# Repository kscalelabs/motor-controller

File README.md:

# K-Scale Motor Controller

## `archive/`
Old motor driver designs

## `pcb/`
New designs, focused on EtherCAT compatibility

No documentation yet (oops) but will show up soon<sup>TM</sup> once I can get some of the motor functions validated

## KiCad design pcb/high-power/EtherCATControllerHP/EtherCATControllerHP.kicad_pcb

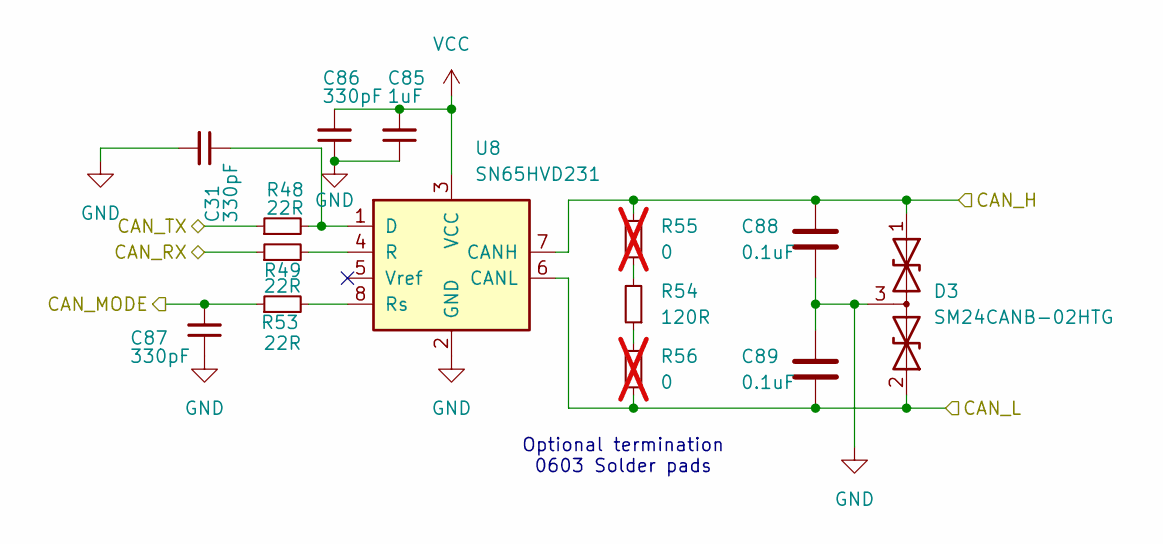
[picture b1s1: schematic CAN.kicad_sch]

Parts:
C31, C86, C87: 330pF; C_0402_1005Metric; LCSC Part # C526998
C85: 1uF; C_0603_1608Metric; LCSC Part # C106858
C88, C89: 0.1uF; C_0603_1608Metric; TOLERANCE ±10%; VOLTAGE - RATED 50V; MANUFACTURER PART NUMBER GRM188R71H104KA93D; LCSC Part # C77055
D3: SM24CANB-02HTG; SOT-23; LCSC Part # C2937019
R48, R49, R53: 22R; R_0603_1608Metric; LCSC Part # C107701
R54: 120R; R_0402_1005Metric; LCSC Part # C114640
R55, R56: 0; R_0603_1608Metric_Pad0.98x0.95mm_HandSolder; not fitted
U8: SN65HVD231; SOIC-8_3.9x4.9mm_P1.27mm; LCSC Part # C129257

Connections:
/CAN_H: C88.1, D3.1 (A1), R55.1, U8.7 (CANH); also elsewhere on the board
/CAN_L: C89.2, D3.2 (A2), R56.2, U8.6 (CANL); also elsewhere on the board
/CAN_MODE: C87.2, R53.1; also elsewhere on the board
/CAN_RX: R49.1; also elsewhere on the board
/CAN_TX: R48.1; also elsewhere on the board
GND: C31.2, C85.1, C86.1, C87.1, C88.2, C89.1, D3.3 (common), U8.2 (GND); also elsewhere on the board
unnamed: R54.1, R56.1
unnamed: R54.2, R55.2
unnamed: C31.1, R48.2, U8.1 (D)
unnamed: R49.2, U8.4 (R)
unnamed: R53.2, U8.8 (Rs)
VCC: C85.2, C86.2, U8.3 (VCC); also elsewhere on the board

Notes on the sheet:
Optional termination 0603 Solder pads

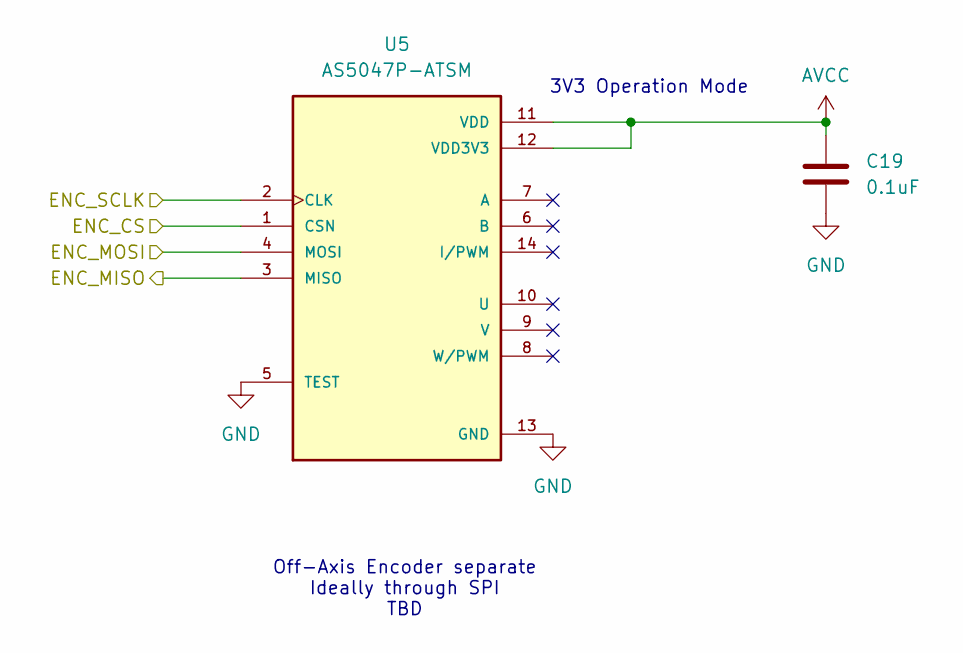
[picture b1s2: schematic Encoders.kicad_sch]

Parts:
C19: 0.1uF; C_0402_1005Metric; LCSC Part # C513772
U5: AS5047P-ATSM; SOP65P640X120-14N; PARTREV 1-01; LCSC Part # C962063

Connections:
/SPI1_CS: U5.1 (CSN); also elsewhere on the board
/SPI1_MISO: U5.3 (MISO); also elsewhere on the board
/SPI1_MOSI: U5.4 (MOSI); also elsewhere on the board
/SPI1_SCK: U5.2 (CLK); also elsewhere on the board
AVCC: C19.1, U5.11 (VDD), U5.12 (VDD3V3); also elsewhere on the board
GND: C19.2, U5.5 (TEST), U5.13 (GND); also elsewhere on the board

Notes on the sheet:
Off-Axis Encoder separate Ideally through SPI TBD
3V3 Operation Mode

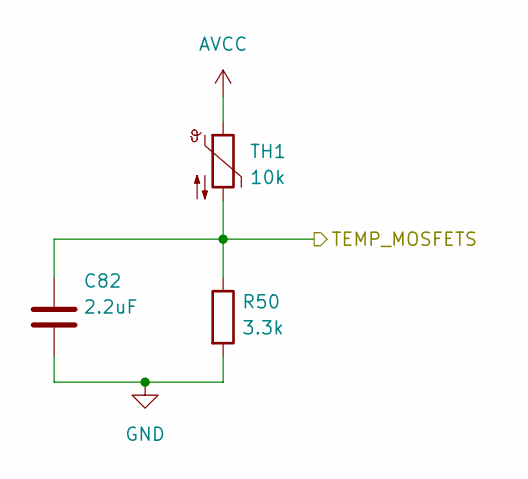
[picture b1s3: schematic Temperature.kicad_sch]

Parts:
C82: 2.2uF; C_0603_1608Metric; TOLERANCE ±10%; VOLTAGE - RATED 16V; MANUFACTURER PART NUMBER GRM188R61C225KE15D; LCSC Part # C77183
R50: 3.3k; R_0603_1608Metric; TOLERANCE ±1%; MANUFACTURER PART NUMBER RC0603FR-073K3L; LCSC Part # C108078
TH1: 10k; R_0402_1005Metric; LCSC Part # C77131

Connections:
/TEMP_MOSFETS: C82.1, R50.1, TH1.2; also elsewhere on the board
AVCC: TH1.1; also elsewhere on the board
GND: C82.2, R50.2; also elsewhere on the board

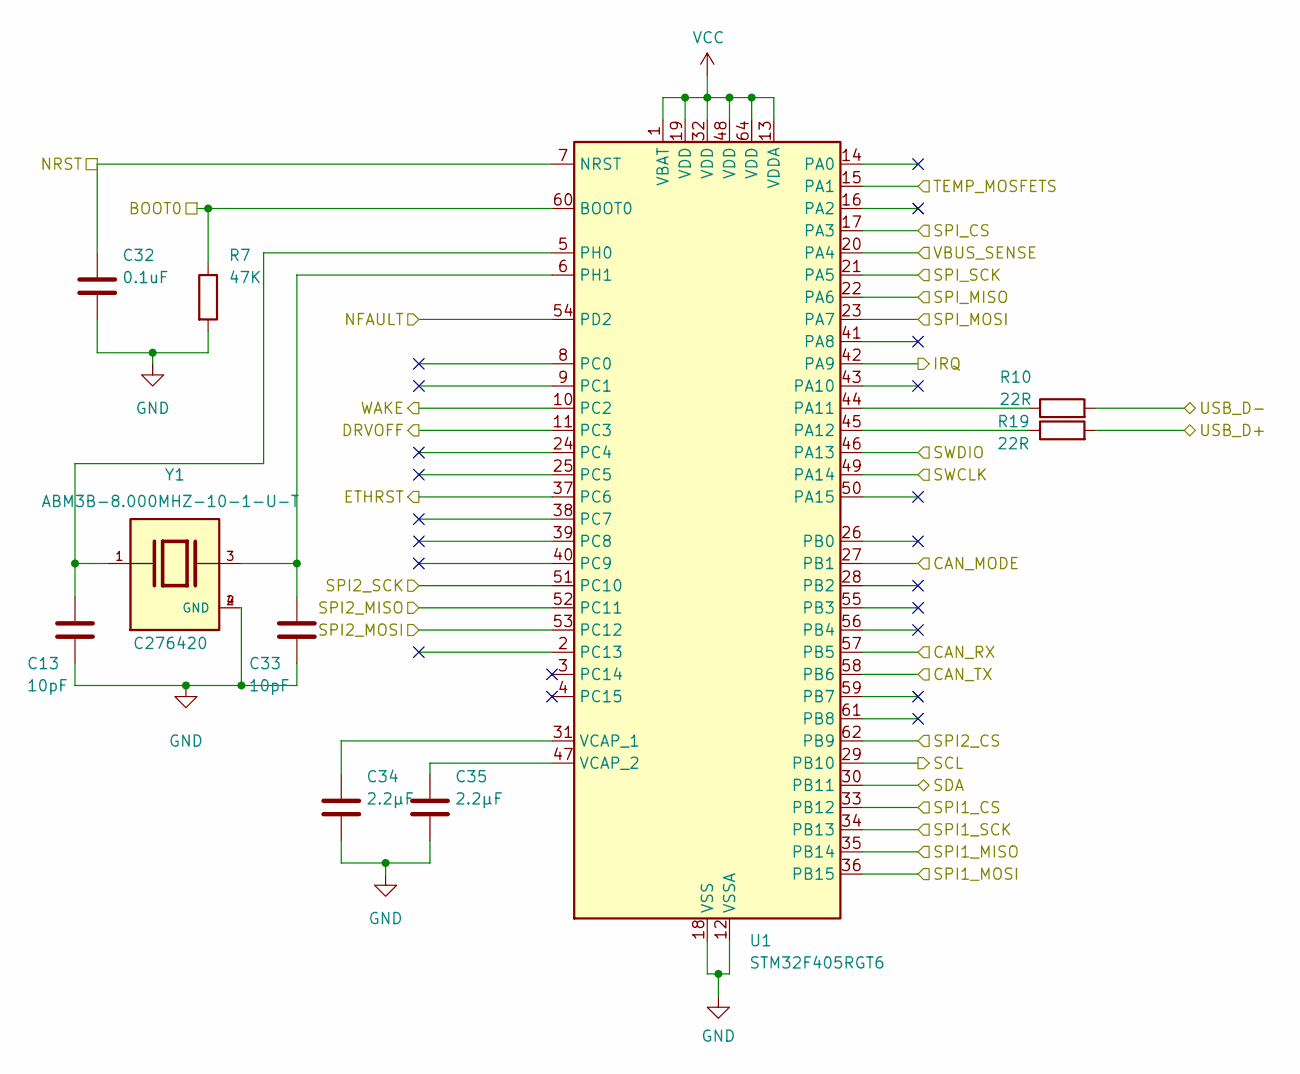
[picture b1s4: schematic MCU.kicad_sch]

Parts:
C13, C33: 10pF; C_0402_1005Metric; TOLERANCE ±5%; VOLTAGE - RATED 50V; MANUFACTURER PART NUMBER GRM1885C1H100JA01D; LCSC Part # C115606
C32: 0.1uF; C_0603_1608Metric; TOLERANCE ±10%; VOLTAGE - RATED 50V; MANUFACTURER PART NUMBER GRM188R71H104KA93D; LCSC Part # C77055
C34, C35: 2.2µF; C_0603_1608Metric; TOLERANCE ±10%; VOLTAGE - RATED 16V; MANUFACTURER PART NUMBER GRM188R61C225KE15D; LCSC Part # C77183
R7: 47K; R_0603_1608Metric; TOLERANCE ±1%; MANUFACTURER PART NUMBER RC0603FR-0747KL; LCSC Part # C105579
R10, R19: 22R; R_0402_1005Metric; LCSC Part # C107701
U1: STM32F405RGT6; LQFP-64_10x10mm_P0.5mm; LCSC Part # C15742
Y1: ABM3B-8.000MHZ-10-1-U-T; Crystal_SMD_5032-4Pin_5.0x3.2mm; PARTREV 08.25.15; LCSC Part # C276420

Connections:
/BOOT0: R7.1, U1.60 (BOOT0); also elsewhere on the board
/CAN_MODE: U1.27 (PB1); also elsewhere on the board
/CAN_RX: U1.57 (PB5); also elsewhere on the board
/CAN_TX: U1.58 (PB6); also elsewhere on the board
/DRVOFF: U1.11 (PC3); also elsewhere on the board
/ETHRST: U1.37 (PC6); also elsewhere on the board
/I2C_SCL: U1.29 (PB10); also elsewhere on the board
/I2C_SDA: U1.30 (PB11); also elsewhere on the board
/IRQ: U1.42 (PA9); also elsewhere on the board
/NFAULT: U1.54 (PD2); also elsewhere on the board
/NRST: C32.1, U1.7 (NRST)
/SPI1_CS: U1.33 (PB12); also elsewhere on the board
/SPI1_MISO: U1.35 (PB14); also elsewhere on the board
/SPI1_MOSI: U1.36 (PB15); also elsewhere on the board
/SPI1_SCK: U1.34 (PB13); also elsewhere on the board
/SPI2_CS: U1.62 (PB9); also elsewhere on the board
/SPI2_MISO: U1.52 (PC11); also elsewhere on the board
/SPI2_MOSI: U1.53 (PC12); also elsewhere on the board
/SPI2_SCK: U1.51 (PC10); also elsewhere on the board
/SPI_CS: U1.17 (PA3); also elsewhere on the board
/SPI_MISO: U1.22 (PA6); also elsewhere on the board
/SPI_MOSI: U1.23 (PA7); also elsewhere on the board
/SPI_SCK: U1.21 (PA5); also elsewhere on the board
/SWCLK: U1.49 (PA14); also elsewhere on the board
/SWDIO: U1.46 (PA13); also elsewhere on the board
/TEMP_MOSFETS: U1.15 (PA1); also elsewhere on the board
/USB_D+: R19.2; also elsewhere on the board
/USB_D-: R10.2; also elsewhere on the board
/VBUS_SENSE: U1.20 (PA4); also elsewhere on the board
/WAKE: U1.10 (PC2); also elsewhere on the board
GND: C13.2, C32.2, C33.2, C34.2, C35.2, R7.2, U1.12 (VSSA), U1.18 (VSS), U1.63 (VSS), Y1.2 (GND), Y1.4 (GND); also elsewhere on the board
unnamed: R10.1, U1.44 (PA11)
unnamed: R19.1, U1.45 (PA12)
unnamed: C13.1, U1.5 (PH0), Y1.1
unnamed: C33.1, U1.6 (PH1), Y1.3
unnamed: C34.1, U1.31 (VCAP_1)
unnamed: C35.1, U1.47 (VCAP_2)
VCC: U1.1 (VBAT), U1.13 (VDDA), U1.19 (VDD), U1.32 (VDD), U1.48 (VDD), U1.64 (VDD); also elsewhere on the board

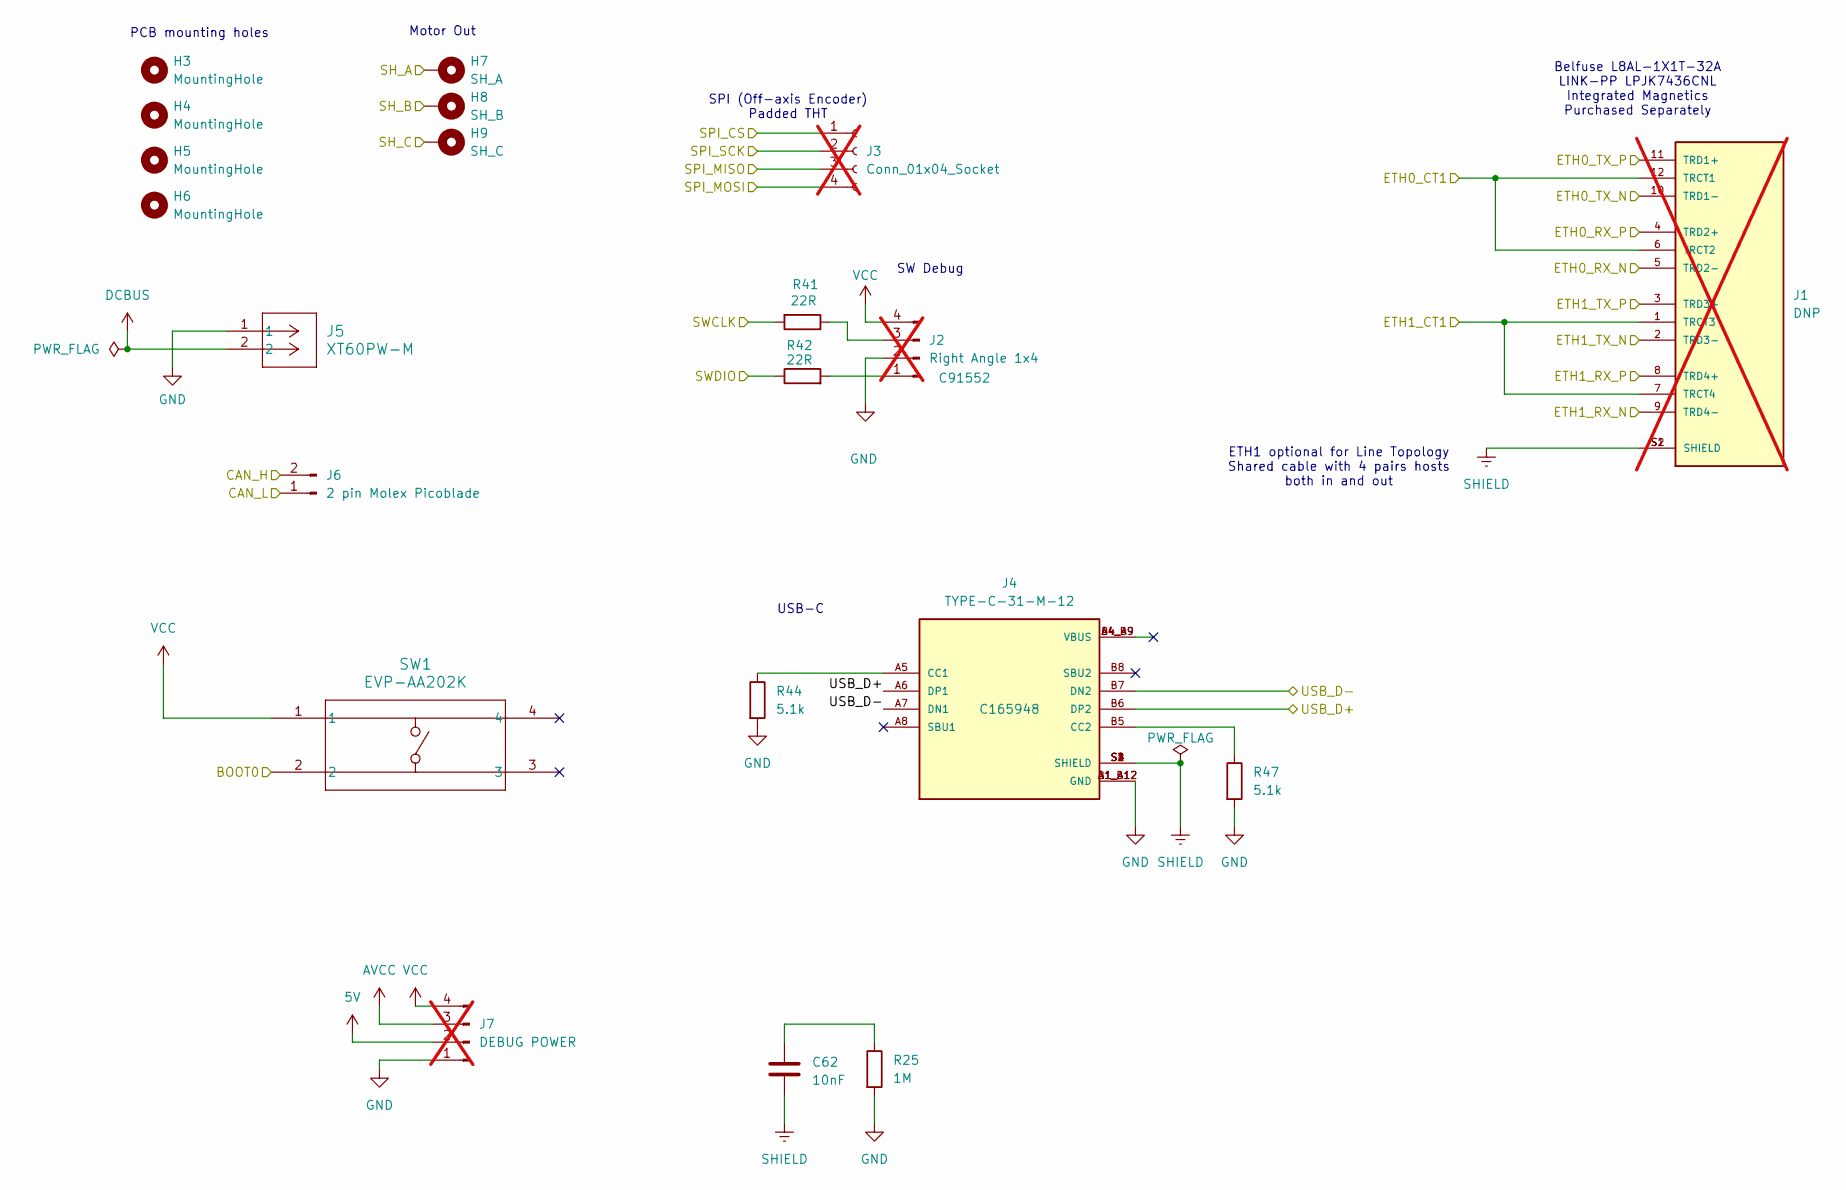
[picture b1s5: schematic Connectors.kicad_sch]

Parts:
C62: 10nF; C_1812_4532Metric; TOLERANCE ±10%; VOLTAGE - RATED 50V; MANUFACTURER PART NUMBER GRM188R71H104KA93D; LCSC Part # C574051
H3, H4, H5, H6: MountingHole; MountingHole_3.2mm_M3_Pad_Via
H7: SH_A; MountingHole_2.2mm_M2_Pad
H8: SH_B; MountingHole_2.2mm_M2_Pad
H9: SH_C; MountingHole_2.2mm_M2_Pad
J1: DNP; BEL_L8AL-1X1T-32A; PARTREV A; not fitted
J2: Right Angle 1x4; PinHeader_1x04_P1.00mm_Vertical; LCSC Part # C91552; not fitted
J3: Conn_01x04_Socket; PinHeader_1x04_P1.00mm_Vertical; not fitted
J4: TYPE-C-31-M-12; HRO_TYPE-C-31-M-12; PARTREV 2020.12.08; LCSC Part # C165948
J5: XT60PW-M; AMASS_XT60PW-M_1x02_P7.20mm_Horizontal; LCSC Part # C98732
J6: 2 pin Molex Picoblade; Molex_PicoBlade_53048-0210_1x02_P1.25mm_Horizontal; LCSC Part # C505099
J7: DEBUG POWER; PinHeader_1x04_P1.00mm_Vertical; not fitted
R25: 1M; R_0402_1005Metric; LCSC Part # C279988
R41, R42: 22R; R_0603_1608Metric; TOLERANCE ±1%; MANUFACTURER PART NUMBER RC0603FR-0722RL; LCSC Part # C107701
R44, R47: 5.1k; R_0603_1608Metric; LCSC Part # C706184
SW1: EVP-AA202K; SW_EVP-AA102K_PAN; LCSC Part # C79147

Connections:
5V: J7.2; also elsewhere on the board
/BOOT0: SW1.2; also elsewhere on the board
/CAN_H: J6.2; also elsewhere on the board
/CAN_L: J6.1; also elsewhere on the board
/ETH0_CT1: J1.6 (TRCT2), J1.12 (TRCT1); also elsewhere on the board
/ETH0_RXN: J1.5 (TRD2-); also elsewhere on the board
/ETH0_RXP: J1.4 (TRD2+); also elsewhere on the board
/ETH0_TXN: J1.10 (TRD1-); also elsewhere on the board
/ETH0_TXP: J1.11 (TRD1+); also elsewhere on the board
/ETH1_CT1: J1.1 (TRCT3), J1.7 (TRCT4); also elsewhere on the board
/ETH1_RXN: J1.9 (TRD4-); also elsewhere on the board
/ETH1_RXP: J1.8 (TRD4+); also elsewhere on the board
/ETH1_TXN: J1.2 (TRD3-); also elsewhere on the board
/ETH1_TXP: J1.3 (TRD3+); also elsewhere on the board
/SPI_CS: J3.1; also elsewhere on the board
/SPI_MISO: J3.3; also elsewhere on the board
/SPI_MOSI: J3.4; also elsewhere on the board
/SPI_SCK: J3.2; also elsewhere on the board
/SWCLK: R41.2; also elsewhere on the board
/SWDIO: R42.1; also elsewhere on the board
/USB_D+: J4.A6 (DP1), J4.B6 (DP2); also elsewhere on the board
/USB_D-: J4.A7 (DN1), J4.B7 (DN2); also elsewhere on the board
AVCC: J7.3; also elsewhere on the board
DCBUS: J5.2; also elsewhere on the board
GND: J2.2, J4.A1_B12 (GND), J4.B1_A12 (GND), J5.1, J7.1, R25.2, R44.2, R47.2; also elsewhere on the board
unnamed: C62.1, R25.1
unnamed: J2.1, R42.2
unnamed: J2.3, R41.1
unnamed: J4.A5 (CC1), R44.1
unnamed: J4.B5 (CC2), R47.1
SHIELD: C62.2, J1.S1 (SHIELD), J1.S2 (SHIELD), J4.S1 (SHIELD), J4.S2 (SHIELD), J4.S3 (SHIELD), J4.S4 (SHIELD)
VCC: J2.4, J7.4, SW1.1; also elsewhere on the board

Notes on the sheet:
SPI (Off-axis Encoder) Padded THT
Motor Out
Belfuse L8AL-1X1T-32A LINK-PP LPJK7436CNL Integrated Magnetics Purchased Separately
ETH1 optional for Line Topology Shared cable with 4 pairs hosts both in and out
USB-C
PCB mounting holes
SW Debug

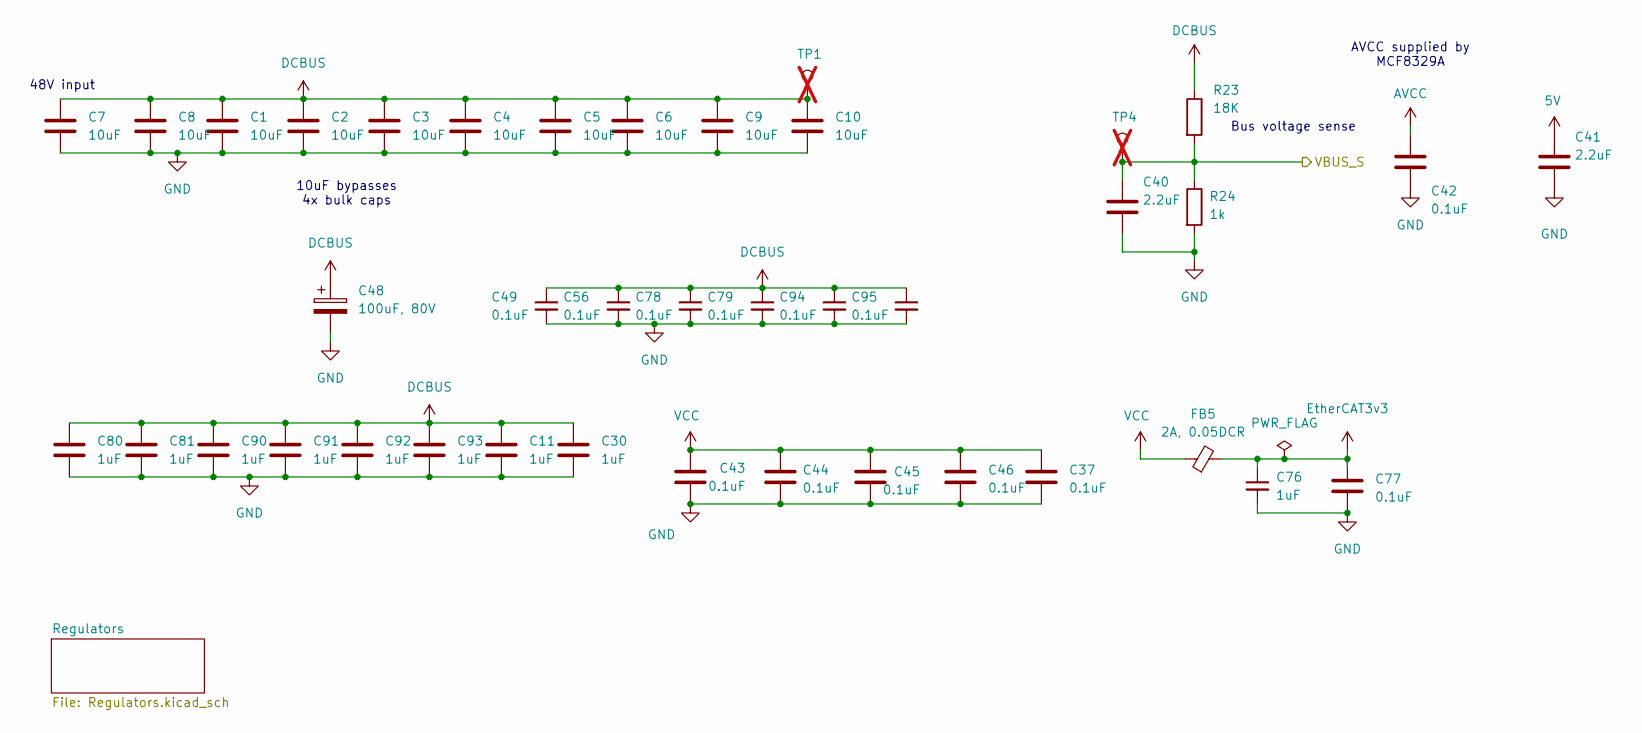
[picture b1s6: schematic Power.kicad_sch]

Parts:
C1, C2, C3, C4, C5, C6, C7, C8, C9, C10: 10uF; C_1210_3225Metric; LCSC Part # C5156756
C11, C30, C80, C81, C90, C91, C92, C93: 1uF; C_1206_3216Metric; LCSC Part # C13832
C37, C43, C44, C45, C46, C77: 0.1uF; C_0603_1608Metric; TOLERANCE ±10%; VOLTAGE - RATED 50V; MANUFACTURER PART NUMBER GRM188R71H104KA93D; LCSC Part # C77055
C40, C41: 2.2uF; C_0603_1608Metric; TOLERANCE ±10%; VOLTAGE - RATED 16V; MANUFACTURER PART NUMBER GRM188R61C225KE15D; LCSC Part # C77183
C42: 0.1uF; C_0603_1608Metric; TOLERANCE ±10%; VOLTAGE - RATED 50V; MANUFACTURER PART NUMBER GRM188R71H104KA93D; LCSC Part # C14663
C48: 100uF, 80V; CP_Elec_10x10; LCSC Part # C487410
C49, C56, C78, C79, C94, C95: 0.1uF; C_0805_2012Metric; LCSC Part # C28233
C76: 1uF; C_0603_1608Metric; LCSC Part # C106858
FB5: 2A, 0.05DCR; L_1206_3216Metric; LCSC Part # C380287
R23: 18K; R_0603_1608Metric; TOLERANCE ±1%; MANUFACTURER PART NUMBER RC0603FR-0710KL; LCSC Part # C98220
R24: 1k; R_0603_1608Metric; TOLERANCE ±1%; MANUFACTURER PART NUMBER RC0603FR-071KL; LCSC Part # C22548
TP1, TP4: TESTPOINT; TestPoint_Pad_1.0x1.0mm; not fitted

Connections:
5V: C41.1; also elsewhere on the board
/VBUS_SENSE: C40.1, R23.2, R24.1, TP4.1; also elsewhere on the board
AVCC: C42.1; also elsewhere on the board
DCBUS: C1.1, C2.1, C3.1, C4.1, C5.1, C6.1, C7.1, C8.1, C9.1, C10.1, C11.1, C30.1, C48.1, C49.1, C56.1, C78.1, C79.1, C80.1, C81.1, C90.1, C91.1, C92.1, C93.1, C94.1, C95.1, R23.1, TP1.1; also elsewhere on the board
EtherCAT3v3: C76.1, C77.1, FB5.2; also elsewhere on the board
GND: C1.2, C2.2, C3.2, C4.2, C5.2, C6.2, C7.2, C8.2, C9.2, C10.2, C11.2, C30.2, C37.2, C40.2, C41.2, C42.2, C43.2, C44.2, C45.2, C46.2, C48.2, C49.2, C56.2, C76.2, C77.2, C78.2, C79.2, C80.2, C81.2, C90.2, C91.2, C92.2, C93.2, C94.2, C95.2, R24.2; also elsewhere on the board
VCC: C37.1, C43.1, C44.1, C45.1, C46.1, FB5.1; also elsewhere on the board

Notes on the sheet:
10uF bypasses 4x bulk caps
48V input
Bus voltage sense
AVCC supplied by MCF8329A

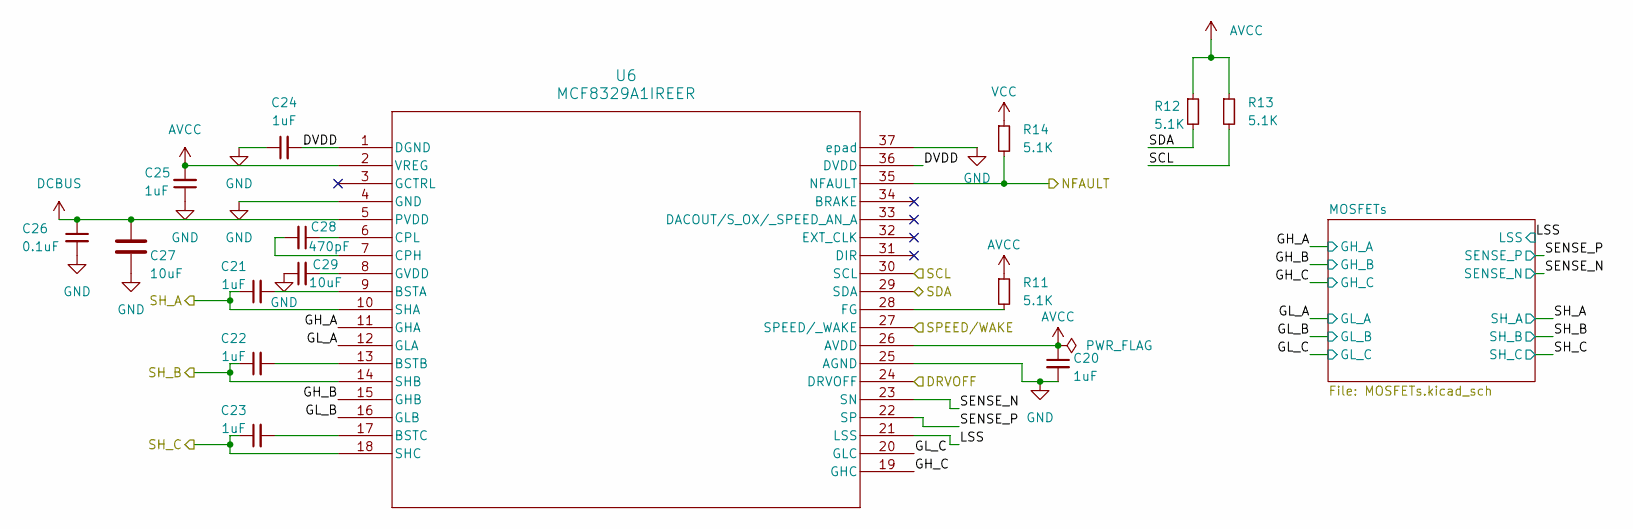
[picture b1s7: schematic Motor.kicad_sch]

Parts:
C20, C24, C25: 1uF; C_0603_1608Metric; LCSC Part # C106858
C21, C22, C23: 1uF; C_0603_1608Metric; LCSC Part # C105174
C26: 0.1uF; C_0805_2012Metric; LCSC Part # C28233
C27: 10uF; C_1210_3225Metric; LCSC Part # C5156756
C28: 470pF; C_0603_1608Metric; LCSC Part # C107062
C29: 10uF; C_0603_1608Metric; LCSC Part # C194427
R11, R12, R13, R14: 5.1K; R_0402_1005Metric; LCSC Part # C105872
U6: MCF8329A1IREER; WQFN36_REE_TEX; LCSC Part # C22399784

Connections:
/DRVOFF: U6.24 (DRVOFF); also elsewhere on the board
/I2C_SCL: R13.2, U6.30 (SCL); also elsewhere on the board
/I2C_SDA: R12.2, U6.29 (SDA); also elsewhere on the board
/Motor/DVDD: C24.2, U6.1 (DGND), U6.36 (DVDD)
/Motor/GH_A: U6.11 (GHA); also elsewhere on the board
/Motor/GH_B: U6.15 (GHB); also elsewhere on the board
/Motor/GH_C: U6.19 (GHC); also elsewhere on the board
/Motor/GL_A: U6.12 (GLA); also elsewhere on the board
/Motor/GL_B: U6.16 (GLB); also elsewhere on the board
/Motor/GL_C: U6.20 (GLC); also elsewhere on the board
/Motor/LSS: U6.21 (LSS); also elsewhere on the board
/Motor/SENSE_N: U6.23 (SN); also elsewhere on the board
/Motor/SENSE_P: U6.22 (SP); also elsewhere on the board
/NFAULT: R14.2, U6.35 (NFAULT); also elsewhere on the board
/SH_A: C21.1, U6.10 (SHA); also elsewhere on the board
/SH_B: C22.1, U6.14 (SHB); also elsewhere on the board
/SH_C: C23.1, U6.18 (SHC); also elsewhere on the board
/WAKE: U6.27 (SPEED/_WAKE); also elsewhere on the board
AVCC: C20.1, C25.2, R11.1, R12.1, R13.1, U6.2 (VREG), U6.26 (AVDD); also elsewhere on the board
DCBUS: C26.1, C27.1, U6.5 (PVDD); also elsewhere on the board
GND: C20.2, C24.1, C25.1, C26.2, C27.2, C29.1, U6.4 (GND), U6.25 (AGND), U6.37 (epad); also elsewhere on the board
unnamed: C21.2, U6.9 (BSTA)
unnamed: C22.2, U6.13 (BSTB)
unnamed: C23.2, U6.17 (BSTC)
unnamed: C28.2, U6.7 (CPH)
unnamed: C28.1, U6.6 (CPL)
unnamed: R11.2, U6.28 (FG)
unnamed: C29.2, U6.8 (GVDD)
VCC: R14.1; also elsewhere on the board

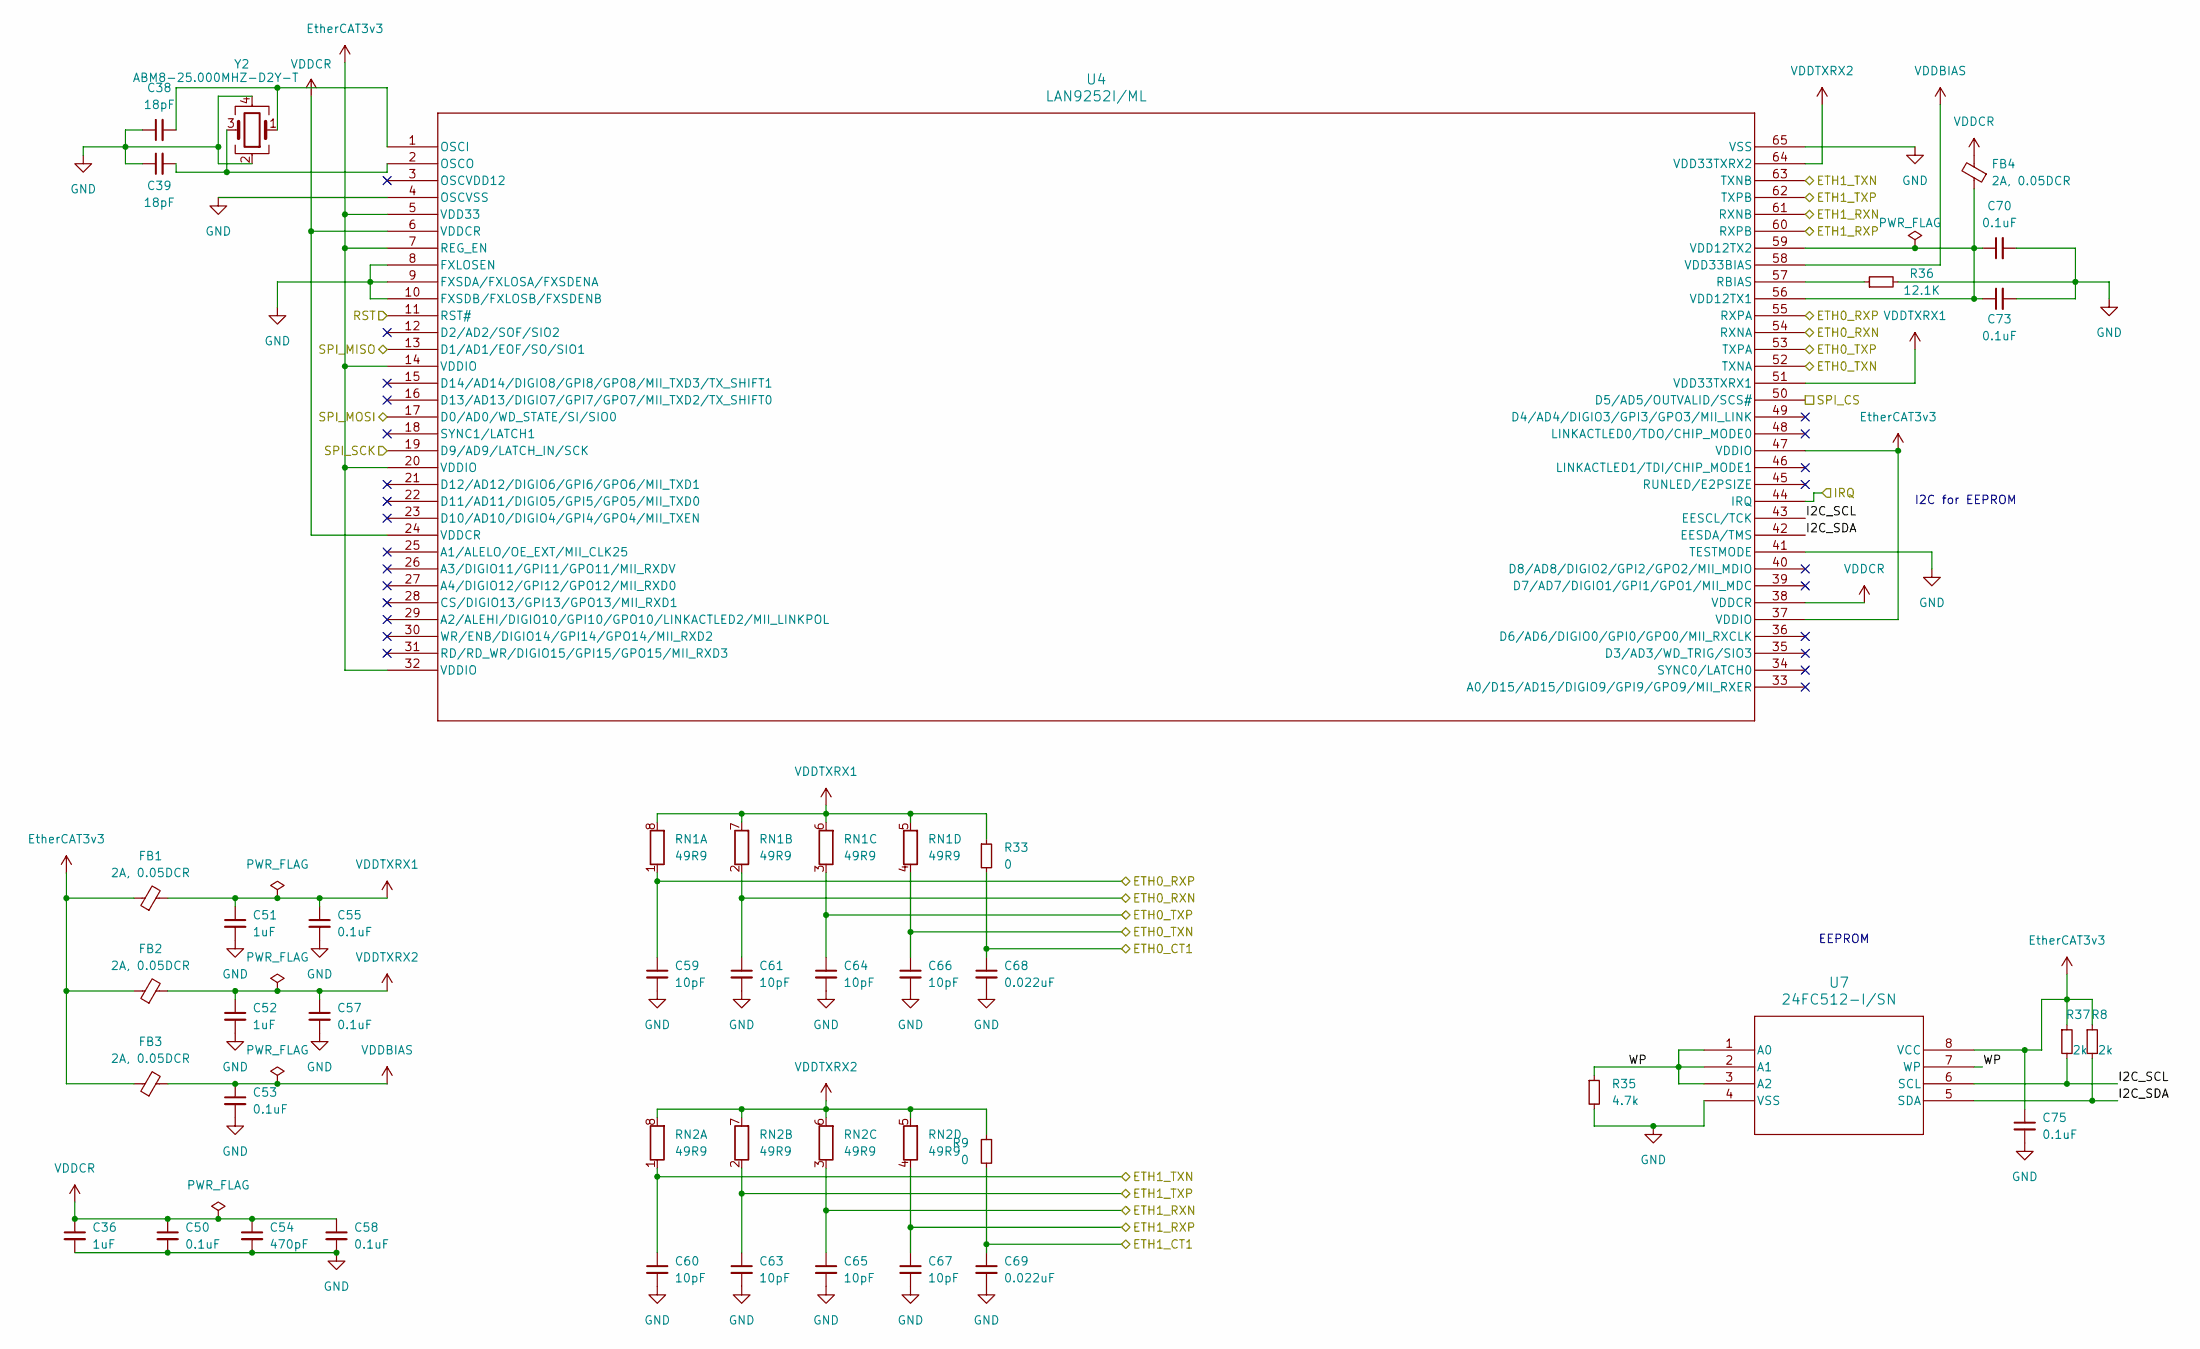
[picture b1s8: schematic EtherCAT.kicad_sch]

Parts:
C36, C51, C52: 1uF; C_0603_1608Metric; LCSC Part # C106858
C38, C39: 18pF; C_0402_1005Metric; LCSC Part # C76701
C50, C53, C55, C57, C58, C70, C73, C75: 0.1uF; C_0603_1608Metric; LCSC Part # C77055
C54: 470pF; C_0402_1005Metric; LCSC Part # C106207
C59, C60, C61, C63, C64, C65, C66, C67: 10pF; C_0402_1005Metric; LCSC Part # C115606
C68, C69: 0.022uF; C_0402_1005Metric; LCSC Part # C147616
FB1, FB2, FB3, FB4: 2A, 0.05DCR; L_1206_3216Metric; LCSC Part # C380287
R8, R37: 2k; R_0402_1005Metric; LCSC Part # C144035
R9, R33: 0; R_0402_1005Metric; LCSC Part # C106231
R35: 4.7k; R_0402_1005Metric; LCSC Part # C105871
R36: 12.1K; R_0402_1005Metric; LCSC Part # C281773
RN1, RN2: 49R9; R_Array_Convex_4x0402; LCSC Part # C136850
U4: LAN9252I/ML; QFN64_ML_MCH; LCSC Part # C2758355
U7: 24FC512-I/SN; SOP-8_3.9x4.9mm_P1.27mm; LCSC Part # C615159
Y2: ABM8-25.000MHZ-D2Y-T; Crystal_SMD_3225-4Pin_3.2x2.5mm; LCSC Part # C179643

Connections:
/ETH0_CT1: C68.1, R33.2; also elsewhere on the board
/ETH0_RXN: C61.1, RN1.2 (R2.1), U4.54 (RXNA); also elsewhere on the board
/ETH0_RXP: C59.1, RN1.1 (R1.1), U4.55 (RXPA); also elsewhere on the board
/ETH0_TXN: C66.1, RN1.4 (R4.1), U4.52 (TXNA); also elsewhere on the board
/ETH0_TXP: C64.1, RN1.3 (R3.1), U4.53 (TXPA); also elsewhere on the board
/ETH1_CT1: C69.1, R9.2; also elsewhere on the board
/ETH1_RXN: C65.1, RN2.3 (R3.1), U4.61 (RXNB); also elsewhere on the board
/ETH1_RXP: C67.1, RN2.4 (R4.1), U4.60 (RXPB); also elsewhere on the board
/ETH1_TXN: C60.1, RN2.1 (R1.1), U4.63 (TXNB); also elsewhere on the board
/ETH1_TXP: C63.1, RN2.2 (R2.1), U4.62 (TXPB); also elsewhere on the board
/ETHRST: U4.11 (RST#); also elsewhere on the board
/EtherCAT/I2C_SCL: R37.2, U4.43 (EESCL/TCK), U7.6 (SCL)
/EtherCAT/I2C_SDA: R8.2, U4.42 (EESDA/TMS), U7.5 (SDA)
/EtherCAT/WP: R35.1, U7.1 (A0), U7.2 (A1), U7.3 (A2), U7.7 (WP)
/IRQ: U4.44 (IRQ); also elsewhere on the board
/SPI2_CS: U4.50 (D5/AD5/OUTVALID/SCS#); also elsewhere on the board
/SPI2_MISO: U4.13 (D1/AD1/EOF/SO/SIO1); also elsewhere on the board
/SPI2_MOSI: U4.17 (D0/AD0/WD_STATE/SI/SIO0); also elsewhere on the board
/SPI2_SCK: U4.19 (D9/AD9/LATCH_IN/SCK); also elsewhere on the board
EtherCAT3v3: C75.1, FB1.1, FB2.1, FB3.1, R8.1, R37.1, U4.5 (VDD33), U4.7 (REG_EN), U4.14 (VDDIO), U4.20 (VDDIO), U4.32 (VDDIO), U4.37 (VDDIO), U4.47 (VDDIO), U7.8 (VCC); also elsewhere on the board
GND: C36.2, C38.1, C39.1, C50.2, C51.2, C52.2, C53.2, C54.2, C55.2, C57.2, C58.2, C59.2, C60.2, C61.2, C63.2, C64.2, C65.2, C66.2, C67.2, C68.2, C69.2, C70.2, C73.2, C75.2, R35.2, R36.2, U4.4 (OSCVSS), U4.8 (FXLOSEN), U4.9 (FXSDA/FXLOSA/FXSDENA), U4.10 (FXSDB/FXLOSB/FXSDENB), U4.41 (TESTMODE), U4.65 (VSS), U7.4 (VSS), Y2.2, Y2.4; also elsewhere on the board
unnamed: C38.2, U4.1 (OSCI), Y2.1
unnamed: C39.2, U4.2 (OSCO), Y2.3
unnamed: R36.1, U4.57 (RBIAS)
unnamed: C70.1, C73.1, FB4.1, U4.56 (VDD12TX1), U4.59 (VDD12TX2)
VDDBIAS: C53.1, FB3.2, U4.58 (VDD33BIAS)
VDDCR: C36.1, C50.1, C54.1, C58.1, FB4.2, U4.6 (VDDCR), U4.24 (VDDCR), U4.38 (VDDCR)
VDDTXRX1: C51.1, C55.1, FB1.2, R33.1, RN1.5 (R4.2), RN1.6 (R3.2), RN1.7 (R2.2), RN1.8 (R1.2), U4.51 (VDD33TXRX1)
VDDTXRX2: C52.1, C57.1, FB2.2, R9.1, RN2.5 (R4.2), RN2.6 (R3.2), RN2.7 (R2.2), RN2.8 (R1.2), U4.64 (VDD33TXRX2)

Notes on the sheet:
EEPROM
I2C for EEPROM

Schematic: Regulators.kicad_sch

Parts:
C12: 4.7uF; C_1210_3225Metric; LCSC Part # C6120033
C14: 0.1uF; C_0402_1005Metric; LCSC Part # C105883
C15: 6800pF; C_0402_1005Metric; LCSC Part # C93654
C16, C17: 4.7uF; C_0805_2012Metric; TOLERANCE ±10%; VOLTAGE - RATED 35V; PART STATUS Active; LCSC Part # C913498
C18: 39pF; C_0402_1005Metric; LCSC Part # C147447
C72, C74: 47uF; C_0805_2012Metric; LCSC Part # C178332
D1: LTST-C190KGKT; D_0603_1608Metric; LCSC Part # C125094
D2: B560C; D_SMC; LCSC Part # C85100
L1: 8.2uH; L_Sunlord_MWSA0603S; LCSC Part # C408450
R1: 162K; R_0603_1608Metric; LCSC Part # C227450
R2: 523K; R_0603_1608Metric_Pad0.98x0.95mm_HandSolder; LCSC Part # C23076
R3: 84.5k; R_0603_1608Metric; LCSC Part # C706195
R4: 13K; R_0402_1005Metric; LCSC Part # C310197
R5: 1k; R_0603_1608Metric; TOLERANCE ±1%; MANUFACTURER PART NUMBER RC0603FR-071KL; LCSC Part # C22548
R38: 53.6K; R_0603_1608Metric; LCSC Part # C177851
R39: 10.2K; R_0402_1005Metric; LCSC Part # C321256
TP2, TP3: TESTPOINT; TestPoint_Pad_1.0x1.0mm; not fitted
U2: TPS54360DDAR; TI_SO-PowerPAD-8_ThermalVias; LCSC Part # C524806
U3: LDL1117S33R; SOT-223; PARTREV 7; LCSC Part # C435835

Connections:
5V: C72.1, C74.1, L1.2, R38.1, TP3.1, U3.3 (VIN); also elsewhere on the board
/Power/Regulators/FB: R38.2, R39.1, U2.5 (FB)
DCBUS: C12.1, R2.1, U2.2 (VIN); also elsewhere on the board
GND: C12.2, C15.2, C16.2, C17.2, C18.2, C72.2, C74.2, D2.2 (A), R1.2, R3.2, R5.2, R39.2, U2.7 (GND), U2.9 (GNDPAD), U3.1 (GND); also elsewhere on the board
unnamed: C15.1, R4.2
unnamed: D1.2, R5.1
unnamed: C14.2, D2.1 (K), L1.1, U2.8 (SW)
unnamed: C14.1, U2.1 (BOOT)
unnamed: C18.1, R4.1, U2.6 (COMP)
unnamed: R2.2, R3.1, U2.3 (EN)
unnamed: R1.1, U2.4 (RT/CLK)
VCC: C16.1, C17.1, D1.1, TP2.1, U3.2 (VOUT), U3.4 (VOUT); also elsewhere on the board

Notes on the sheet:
3v3
5V out

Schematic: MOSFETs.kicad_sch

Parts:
NT1, NT2: NetTie_2; NetTie-2_SMD_Pad2.0mm
Q1, Q2, Q3, Q4, Q5, Q6, Q7, Q8, Q9, Q10, Q11, Q12: ONSemi_SO-8FL_488AA; DRIVE VOLTAGE (MAX RDS 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 4.5V, 10V; PART STATUS Active; LCSC Part # C348543
R6: 500uOhm; R_2512_6332Metric; TOLERANCE ±1%; PART STATUS Active; LCSC Part # C500733
R15, R16, R17, R18, R20, R21: 2.2R; R_0603_1608Metric; TOLERANCE ±1%; MANUFACTURER PART NUMBER RC0603FR-072R2L; LCSC Part # C112307

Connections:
/Motor/GH_A: R15.2; also elsewhere on the board
/Motor/GH_B: R18.2; also elsewhere on the board
/Motor/GH_C: R20.2; also elsewhere on the board
/Motor/GL_A: R16.1; also elsewhere on the board
/Motor/GL_B: R17.2; also elsewhere on the board
/Motor/GL_C: R21.1; also elsewhere on the board
/Motor/LSS: NT2.1, Q2.1 (S), Q2.2 (S), Q2.3 (S), Q6.1 (S), Q6.2 (S), Q6.3 (S), Q8.1 (S), Q8.2 (S), Q8.3 (S), Q10.1 (S), Q10.2 (S), Q10.3 (S), Q11.1 (S), Q11.2 (S), Q11.3 (S), Q12.1 (S), Q12.2 (S), Q12.3 (S), R6.1; also elsewhere on the board
/Motor/SENSE_N: NT1.2; also elsewhere on the board
/Motor/SENSE_P: NT2.2; also elsewhere on the board
/SH_A: Q1.1 (S), Q1.2 (S), Q1.3 (S), Q2.5 (D), Q3.1 (S), Q3.2 (S), Q3.3 (S), Q8.5 (D); also elsewhere on the board
/SH_B: Q4.1 (S), Q4.2 (S), Q4.3 (S), Q5.1 (S), Q5.2 (S), Q5.3 (S), Q6.5 (D), Q11.5 (D); also elsewhere on the board
/SH_C: Q7.1 (S), Q7.2 (S), Q7.3 (S), Q9.1 (S), Q9.2 (S), Q9.3 (S), Q10.5 (D), Q12.5 (D); also elsewhere on the board
DCBUS: Q1.5 (D), Q3.5 (D), Q4.5 (D), Q5.5 (D), Q7.5 (D), Q9.5 (D); also elsewhere on the board
GND: NT1.1, R6.2; also elsewhere on the board
unnamed: Q1.4 (G), Q3.4 (G), R15.1
unnamed: Q2.4 (G), Q8.4 (G), R16.2
unnamed: Q4.4 (G), Q5.4 (G), R18.1
unnamed: Q7.4 (G), Q9.4 (G), R20.1
unnamed: Q10.4 (G), Q12.4 (G), R21.2
unnamed: Q6.4 (G), Q11.4 (G), R17.1

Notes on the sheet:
MOSFETS: NTMFS5C612NLT1G 60V, 36A Ta Downsized for low-power variant
